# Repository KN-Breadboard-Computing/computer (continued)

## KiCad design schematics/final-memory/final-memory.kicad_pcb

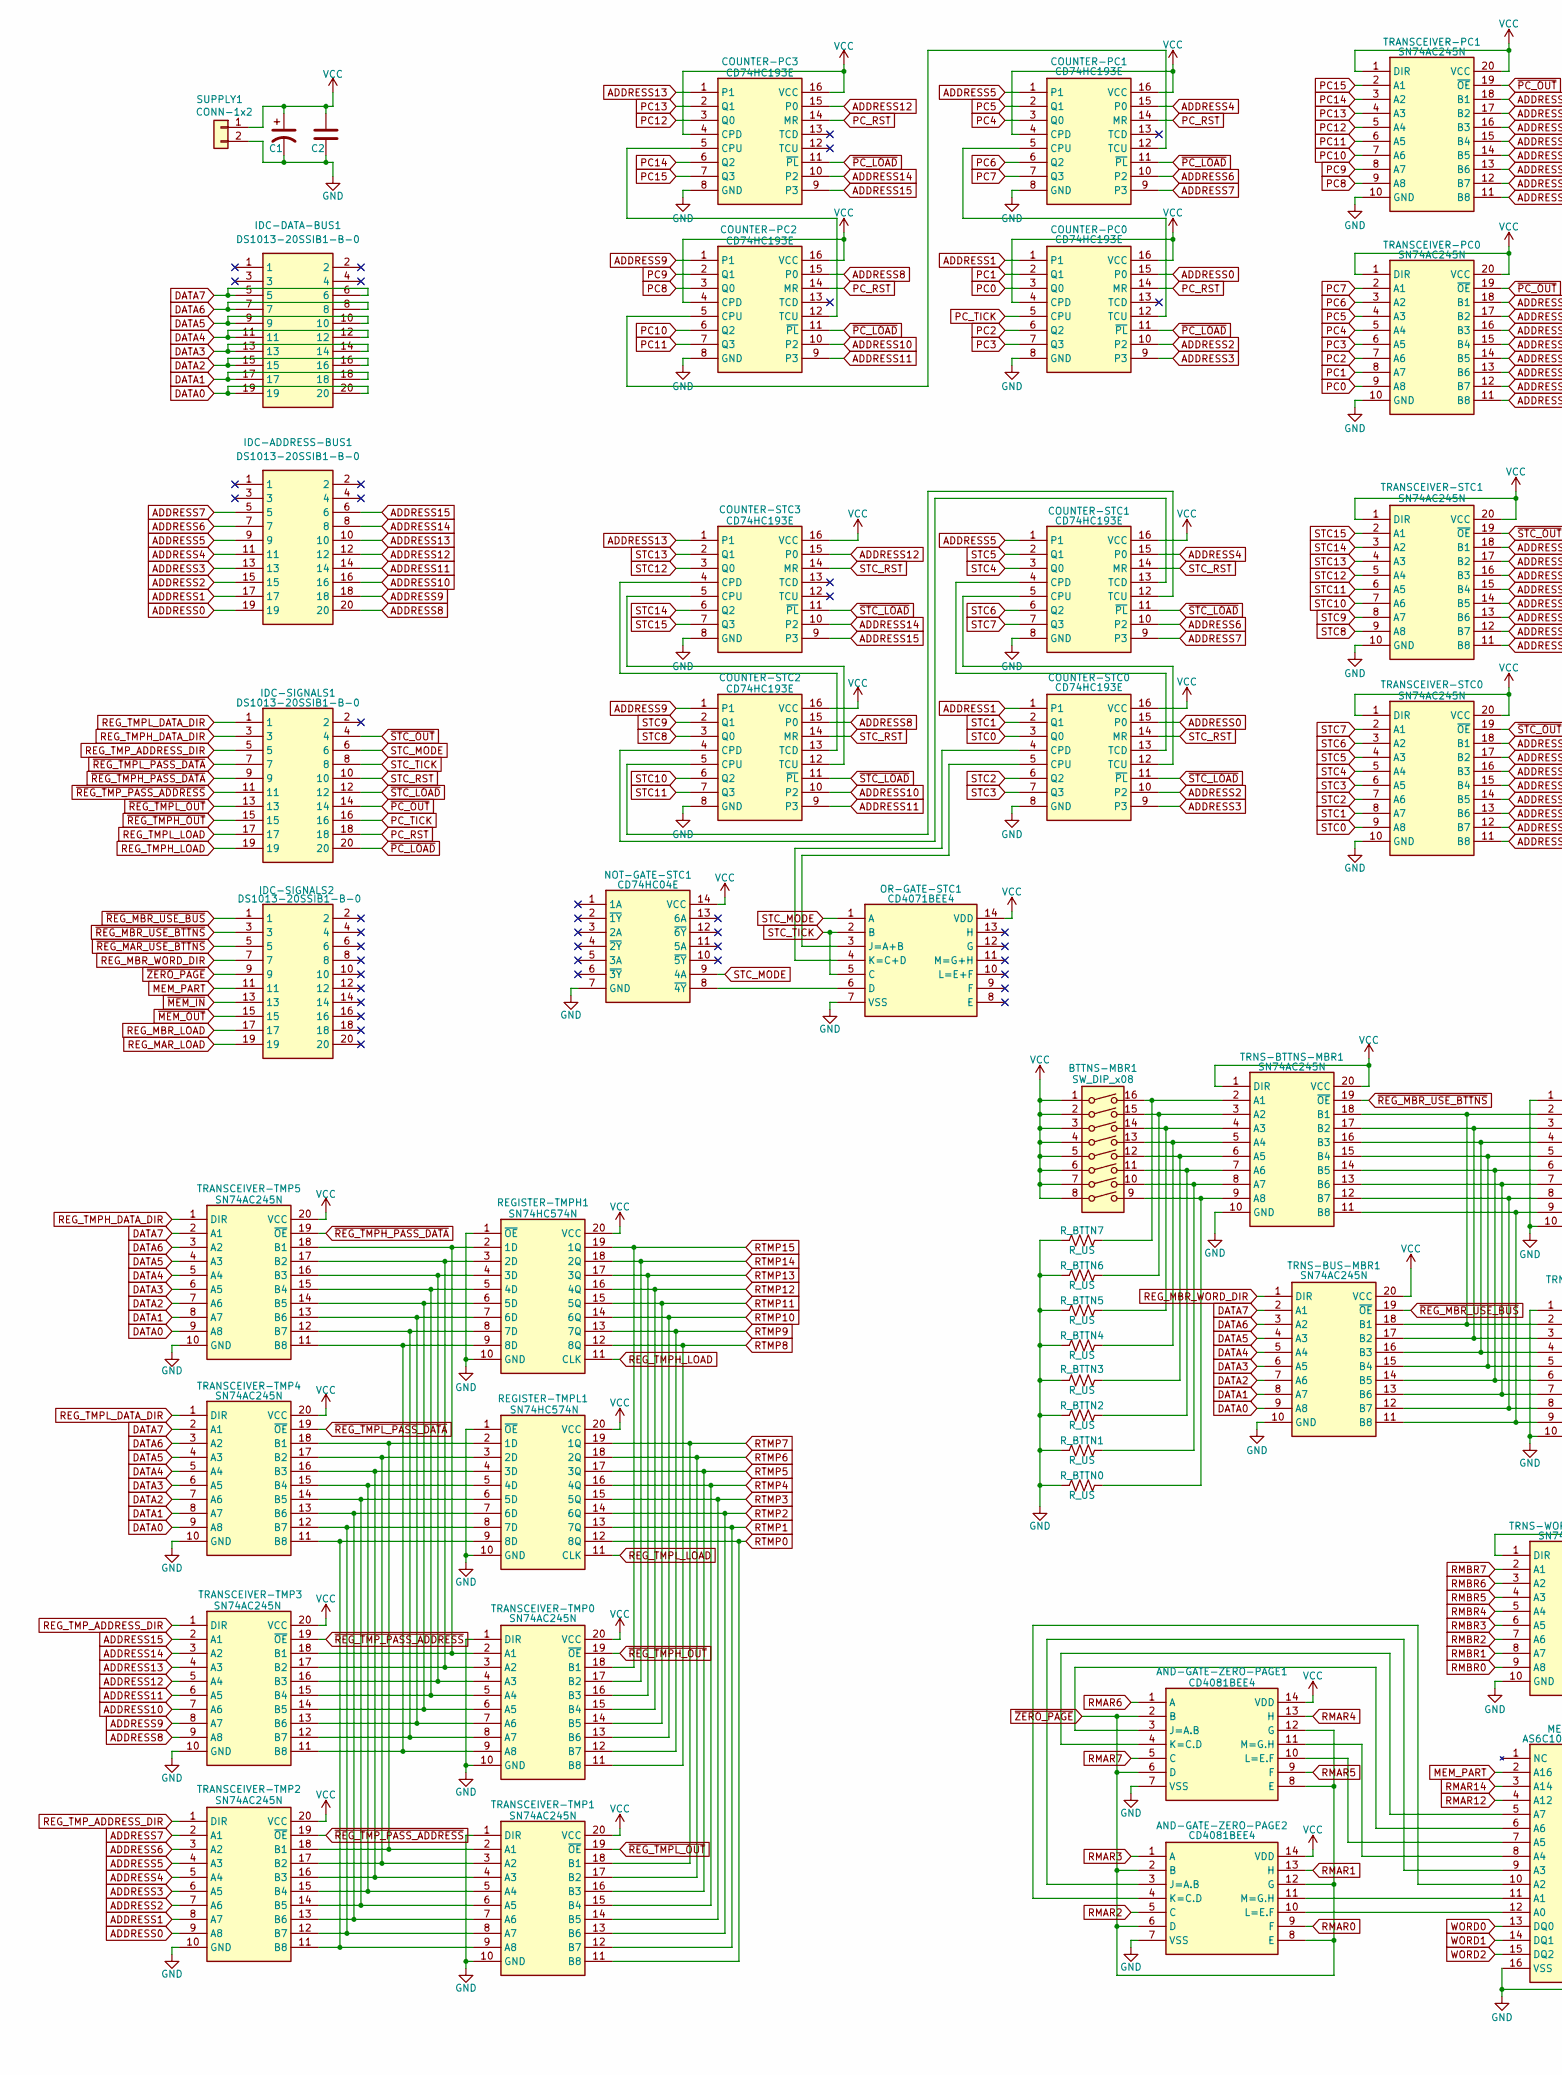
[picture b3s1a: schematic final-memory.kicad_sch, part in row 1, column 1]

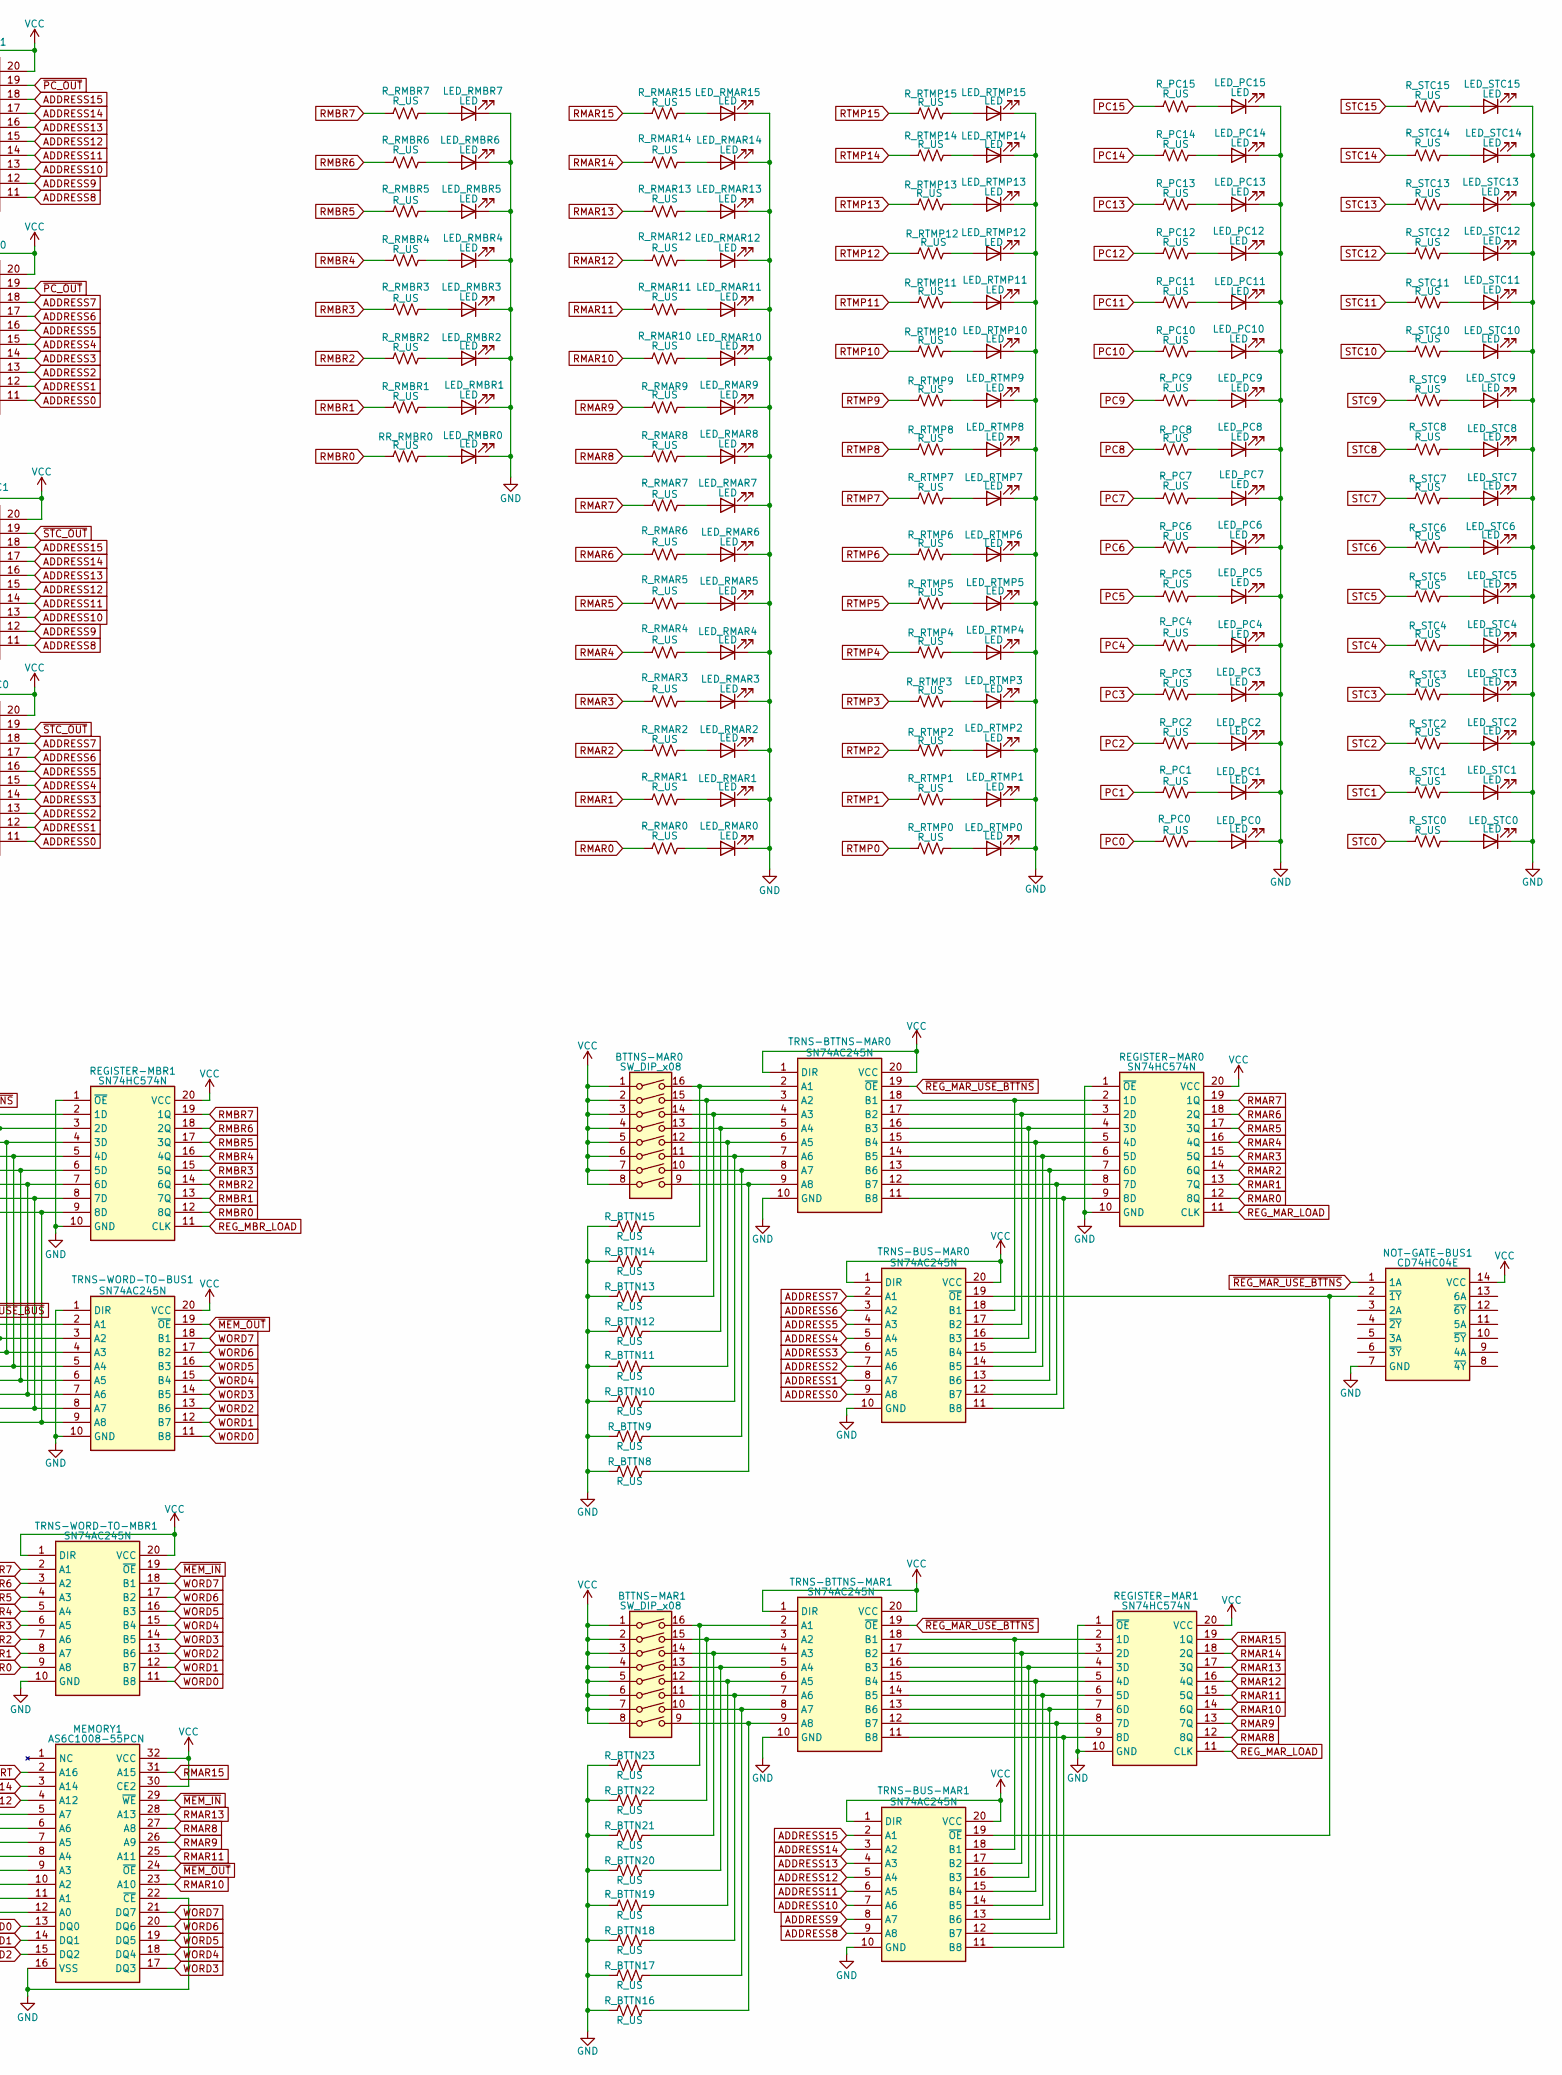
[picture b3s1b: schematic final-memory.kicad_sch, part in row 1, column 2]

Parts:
AND-GATE-ZERO-PAGE1, AND-GATE-ZERO-PAGE2: CD4081BEE4; DIP-14_W7.62mm; Mouser Part Number 595-CD4081BEE4
BTTNS-MAR0, BTTNS-MAR1: SW_DIP_x08; SW_DIP_SPSTx08_Slide_6.7x21.88mm_W7.62mm_P2.54mm_LowProfile
BTTNS-MBR1: SW_DIP_x08; SW_DIP_SPSTx08_Slide_6.7x21.88mm_W7.62mm_P2.54mm_LowProfile
C1: C_Polarized_US; CP_Radial_D5.0mm_P2.50mm
C2: C; C_Disc_D3.0mm_W1.6mm_P2.50mm
COUNTER-PC0, COUNTER-PC1, COUNTER-PC2, COUNTER-PC3: CD74HC193E; DIP-16_W7.62mm; Mouser Part Number 595-CD74HC193E
COUNTER-STC0, COUNTER-STC1, COUNTER-STC2, COUNTER-STC3: CD74HC193E; DIP-16_W7.62mm; Mouser Part Number 595-CD74HC193E
IDC-ADDRESS-BUS1: DS1013-20SSIB1-B-0; PinSocket_2x10_P2.54mm_Vertical; Manufacturer_Part_Number DS1013-20SSIB1-B-0
IDC-DATA-BUS1: DS1013-20SSIB1-B-0; PinSocket_2x10_P2.54mm_Vertical; Manufacturer_Part_Number DS1013-20SSIB1-B-0
IDC-SIGNALS1, IDC-SIGNALS2: DS1013-20SSIB1-B-0; PinSocket_2x10_P2.54mm_Vertical; Manufacturer_Part_Number DS1013-20SSIB1-B-0
LED_PC0, LED_PC1, LED_PC2, LED_PC3, LED_PC4, LED_PC5, LED_PC6, LED_PC7, LED_PC8, LED_PC9, LED_PC10, LED_PC11, LED_PC12, LED_PC13, LED_PC14, LED_PC15: LED; LED_D5.0mm_FlatTop
LED_RMAR0, LED_RMAR1, LED_RMAR2, LED_RMAR3, LED_RMAR4, LED_RMAR5, LED_RMAR6, LED_RMAR7, LED_RMAR8, LED_RMAR9, LED_RMAR10, LED_RMAR11, LED_RMAR12, LED_RMAR13, LED_RMAR14, LED_RMAR15: LED; LED_D5.0mm_FlatTop
LED_RMBR0, LED_RMBR1, LED_RMBR2, LED_RMBR3, LED_RMBR4, LED_RMBR5, LED_RMBR6, LED_RMBR7: LED; LED_D5.0mm_FlatTop
LED_RTMP0, LED_RTMP1, LED_RTMP2, LED_RTMP3, LED_RTMP4, LED_RTMP5, LED_RTMP6, LED_RTMP7, LED_RTMP8, LED_RTMP9, LED_RTMP10, LED_RTMP11, LED_RTMP12, LED_RTMP13, LED_RTMP14, LED_RTMP15: LED; LED_D5.0mm_FlatTop
LED_STC0, LED_STC1, LED_STC2, LED_STC3, LED_STC4, LED_STC5, LED_STC6, LED_STC7, LED_STC8, LED_STC9, LED_STC10, LED_STC11, LED_STC12, LED_STC13, LED_STC14, LED_STC15: LED; LED_D5.0mm_FlatTop
MEMORY1: AS6C1008-55PCN; DIP-32_W15.24mm; Mouser Part Number 913-AS6C1008-55PCN
NOT-GATE-BUS1: CD74HC04E; DIP-14_W7.62mm; Mouser Part Number 595-CD74HC04E
NOT-GATE-STC1: CD74HC04E; DIP-14_W7.62mm; Mouser Part Number 595-CD74HC04E
OR-GATE-STC1: CD4071BEE4; DIP-14_W7.62mm; Mouser Part Number 595-CD4071BEE4
REGISTER-MAR0, REGISTER-MAR1: SN74HC574N; DIP-20_W7.62mm; Mouser Part Number 595-SN74HC574N
REGISTER-MBR1: SN74HC574N; DIP-20_W7.62mm; Mouser Part Number 595-SN74HC574N
REGISTER-TMPH1: SN74HC574N; DIP-20_W7.62mm; Mouser Part Number 595-SN74HC574N
REGISTER-TMPL1: SN74HC574N; DIP-20_W7.62mm; Mouser Part Number 595-SN74HC574N
RR_RMBR0: R_US; R_Axial_DIN0204_L3.6mm_D1.6mm_P7.62mm_Horizontal
R_BTTN0, R_BTTN1, R_BTTN2, R_BTTN3, R_BTTN4, R_BTTN5, R_BTTN6, R_BTTN7, R_BTTN8, R_BTTN9, R_BTTN10, R_BTTN11, R_BTTN12, R_BTTN13, R_BTTN14, R_BTTN15, R_BTTN16, R_BTTN17, R_BTTN18, R_BTTN19, R_BTTN20, R_BTTN21, R_BTTN22, R_BTTN23: R_US; R_Axial_DIN0204_L3.6mm_D1.6mm_P7.62mm_Horizontal
R_PC0, R_PC1, R_PC2, R_PC3, R_PC4, R_PC5, R_PC6, R_PC7, R_PC8, R_PC9, R_PC10, R_PC11, R_PC12, R_PC13, R_PC14, R_PC15: R_US; R_Axial_DIN0204_L3.6mm_D1.6mm_P7.62mm_Horizontal
R_RMAR0, R_RMAR1, R_RMAR2, R_RMAR3, R_RMAR4, R_RMAR5, R_RMAR6, R_RMAR7, R_RMAR8, R_RMAR9, R_RMAR10, R_RMAR11, R_RMAR12, R_RMAR13, R_RMAR14, R_RMAR15: R_US; R_Axial_DIN0204_L3.6mm_D1.6mm_P7.62mm_Horizontal
R_RMBR1, R_RMBR2, R_RMBR3, R_RMBR4, R_RMBR5, R_RMBR6, R_RMBR7: R_US; R_Axial_DIN0204_L3.6mm_D1.6mm_P7.62mm_Horizontal
R_RTMP0, R_RTMP1, R_RTMP2, R_RTMP3, R_RTMP4, R_RTMP5, R_RTMP6, R_RTMP7, R_RTMP8, R_RTMP9, R_RTMP10, R_RTMP11, R_RTMP12, R_RTMP13, R_RTMP14, R_RTMP15: R_US; R_Axial_DIN0204_L3.6mm_D1.6mm_P7.62mm_Horizontal
R_STC0, R_STC1, R_STC2, R_STC3, R_STC4, R_STC5, R_STC6, R_STC7, R_STC8, R_STC9, R_STC10, R_STC11, R_STC12, R_STC13, R_STC14, R_STC15: R_US; R_Axial_DIN0204_L3.6mm_D1.6mm_P7.62mm_Horizontal
SUPPLY1: CONN-1x2; PinHeader_1x02_P2.54mm_Vertical
TRANSCEIVER-PC0, TRANSCEIVER-PC1: SN74AC245N; DIP-20_W7.62mm; Mouser Part Number 595-SN74AC245N
TRANSCEIVER-STC0, TRANSCEIVER-STC1: SN74AC245N; DIP-20_W7.62mm; Mouser Part Number 595-SN74AC245N
TRANSCEIVER-TMP0, TRANSCEIVER-TMP1, TRANSCEIVER-TMP2, TRANSCEIVER-TMP3, TRANSCEIVER-TMP4, TRANSCEIVER-TMP5: SN74AC245N; DIP-20_W7.62mm; Mouser Part Number 595-SN74AC245N
TRNS-BTTNS-MAR0, TRNS-BTTNS-MAR1: SN74AC245N; DIP-20_W7.62mm; Mouser Part Number 595-SN74AC245N
TRNS-BTTNS-MBR1: SN74AC245N; DIP-20_W7.62mm; Mouser Part Number 595-SN74AC245N
TRNS-BUS-MAR0, TRNS-BUS-MAR1: SN74AC245N; DIP-20_W7.62mm; Mouser Part Number 595-SN74AC245N
TRNS-BUS-MBR1: SN74AC245N; DIP-20_W7.62mm; Mouser Part Number 595-SN74AC245N
TRNS-WORD-TO-BUS1: SN74AC245N; DIP-20_W7.62mm; Mouser Part Number 595-SN74AC245N
TRNS-WORD-TO-MBR1: SN74AC245N; DIP-20_W7.62mm; Mouser Part Number 595-SN74AC245N

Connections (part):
ADDRESS0: COUNTER-PC0.15 (P0), COUNTER-STC0.15 (P0), IDC-ADDRESS-BUS1.19, TRANSCEIVER-PC0.11 (B8), TRANSCEIVER-STC0.11 (B8), TRANSCEIVER-TMP2.9 (A8), TRNS-BUS-MAR0.9 (A8)
ADDRESS1: COUNTER-PC0.1, COUNTER-STC0.1, IDC-ADDRESS-BUS1.17, TRANSCEIVER-PC0.12 (B7), TRANSCEIVER-STC0.12 (B7), TRANSCEIVER-TMP2.8 (A7), TRNS-BUS-MAR0.8 (A7)
ADDRESS2: COUNTER-PC0.10 (P2), COUNTER-STC0.10 (P2), IDC-ADDRESS-BUS1.15, TRANSCEIVER-PC0.13 (B6), TRANSCEIVER-STC0.13 (B6), TRANSCEIVER-TMP2.7 (A6), TRNS-BUS-MAR0.7 (A6)
ADDRESS3: COUNTER-PC0.9 (P3), COUNTER-STC0.9 (P3), IDC-ADDRESS-BUS1.13, TRANSCEIVER-PC0.14 (B5), TRANSCEIVER-STC0.14 (B5), TRANSCEIVER-TMP2.6 (A5), TRNS-BUS-MAR0.6 (A5)
ADDRESS4: COUNTER-PC1.15 (P0), COUNTER-STC1.15 (P0), IDC-ADDRESS-BUS1.11, TRANSCEIVER-PC0.15 (B4), TRANSCEIVER-STC0.15 (B4), TRANSCEIVER-TMP2.5 (A4), TRNS-BUS-MAR0.5 (A4)
ADDRESS5: COUNTER-PC1.1, COUNTER-STC1.1, IDC-ADDRESS-BUS1.9, TRANSCEIVER-PC0.16 (B3), TRANSCEIVER-STC0.16 (B3), TRANSCEIVER-TMP2.4 (A3), TRNS-BUS-MAR0.4 (A3)
ADDRESS6: COUNTER-PC1.10 (P2), COUNTER-STC1.10 (P2), IDC-ADDRESS-BUS1.7, TRANSCEIVER-PC0.17 (B2), TRANSCEIVER-STC0.17 (B2), TRANSCEIVER-TMP2.3 (A2), TRNS-BUS-MAR0.3 (A2)
ADDRESS7: COUNTER-PC1.9 (P3), COUNTER-STC1.9 (P3), IDC-ADDRESS-BUS1.5, TRANSCEIVER-PC0.18 (B1), TRANSCEIVER-STC0.18 (B1), TRANSCEIVER-TMP2.2 (A1), TRNS-BUS-MAR0.2 (A1)
ADDRESS8: COUNTER-PC2.15 (P0), COUNTER-STC2.15 (P0), IDC-ADDRESS-BUS1.20, TRANSCEIVER-PC1.11 (B8), TRANSCEIVER-STC1.11 (B8), TRANSCEIVER-TMP3.9 (A8), TRNS-BUS-MAR1.9 (A8)
ADDRESS9: COUNTER-PC2.1, COUNTER-STC2.1, IDC-ADDRESS-BUS1.18, TRANSCEIVER-PC1.12 (B7), TRANSCEIVER-STC1.12 (B7), TRANSCEIVER-TMP3.8 (A7), TRNS-BUS-MAR1.8 (A7)
ADDRESS10: COUNTER-PC2.10 (P2), COUNTER-STC2.10 (P2), IDC-ADDRESS-BUS1.16, TRANSCEIVER-PC1.13 (B6), TRANSCEIVER-STC1.13 (B6), TRANSCEIVER-TMP3.7 (A6), TRNS-BUS-MAR1.7 (A6)
ADDRESS11: COUNTER-PC2.9 (P3), COUNTER-STC2.9 (P3), IDC-ADDRESS-BUS1.14, TRANSCEIVER-PC1.14 (B5), TRANSCEIVER-STC1.14 (B5), TRANSCEIVER-TMP3.6 (A5), TRNS-BUS-MAR1.6 (A5)
ADDRESS12: COUNTER-PC3.15 (P0), COUNTER-STC3.15 (P0), IDC-ADDRESS-BUS1.12, TRANSCEIVER-PC1.15 (B4), TRANSCEIVER-STC1.15 (B4), TRANSCEIVER-TMP3.5 (A4), TRNS-BUS-MAR1.5 (A4)
ADDRESS13: COUNTER-PC3.1, COUNTER-STC3.1, IDC-ADDRESS-BUS1.10, TRANSCEIVER-PC1.16 (B3), TRANSCEIVER-STC1.16 (B3), TRANSCEIVER-TMP3.4 (A3), TRNS-BUS-MAR1.4 (A3)
ADDRESS14: COUNTER-PC3.10 (P2), COUNTER-STC3.10 (P2), IDC-ADDRESS-BUS1.8, TRANSCEIVER-PC1.17 (B2), TRANSCEIVER-STC1.17 (B2), TRANSCEIVER-TMP3.3 (A2), TRNS-BUS-MAR1.3 (A2)
ADDRESS15: COUNTER-PC3.9 (P3), COUNTER-STC3.9 (P3), IDC-ADDRESS-BUS1.6, TRANSCEIVER-PC1.18 (B1), TRANSCEIVER-STC1.18 (B1), TRANSCEIVER-TMP3.2 (A1), TRNS-BUS-MAR1.2 (A1)
DATA0: IDC-DATA-BUS1.19, IDC-DATA-BUS1.20, TRANSCEIVER-TMP4.9 (A8), TRANSCEIVER-TMP5.9 (A8), TRNS-BUS-MBR1.9 (A8)
DATA1: IDC-DATA-BUS1.17, IDC-DATA-BUS1.18, TRANSCEIVER-TMP4.8 (A7), TRANSCEIVER-TMP5.8 (A7), TRNS-BUS-MBR1.8 (A7)
DATA2: IDC-DATA-BUS1.15, IDC-DATA-BUS1.16, TRANSCEIVER-TMP4.7 (A6), TRANSCEIVER-TMP5.7 (A6), TRNS-BUS-MBR1.7 (A6)
DATA3: IDC-DATA-BUS1.13, IDC-DATA-BUS1.14, TRANSCEIVER-TMP4.6 (A5), TRANSCEIVER-TMP5.6 (A5), TRNS-BUS-MBR1.6 (A5)
DATA4: IDC-DATA-BUS1.11, IDC-DATA-BUS1.12, TRANSCEIVER-TMP4.5 (A4), TRANSCEIVER-TMP5.5 (A4), TRNS-BUS-MBR1.5 (A4)
DATA5: IDC-DATA-BUS1.9, IDC-DATA-BUS1.10, TRANSCEIVER-TMP4.4 (A3), TRANSCEIVER-TMP5.4 (A3), TRNS-BUS-MBR1.4 (A3)
DATA6: IDC-DATA-BUS1.7, IDC-DATA-BUS1.8, TRANSCEIVER-TMP4.3 (A2), TRANSCEIVER-TMP5.3 (A2), TRNS-BUS-MBR1.3 (A2)
DATA7: IDC-DATA-BUS1.5, IDC-DATA-BUS1.6, TRANSCEIVER-TMP4.2 (A1), TRANSCEIVER-TMP5.2 (A1), TRNS-BUS-MBR1.2 (A1)
GND: AND-GATE-ZERO-PAGE1.7 (VSS), AND-GATE-ZERO-PAGE2.7 (VSS), C1.2, C2.2, COUNTER-PC0.8 (GND), COUNTER-PC1.8 (GND), COUNTER-PC2.8 (GND), COUNTER-PC3.8 (GND), COUNTER-STC0.8 (GND), COUNTER-STC1.8 (GND), COUNTER-STC2.8 (GND), COUNTER-STC3.8 (GND), LED_PC0.1 (K), LED_PC1.1 (K), LED_PC2.1 (K), LED_PC3.1 (K), LED_PC4.1 (K), LED_PC5.1 (K), LED_PC6.1 (K), LED_PC7.1 (K), LED_PC8.1 (K), LED_PC9.1 (K), LED_PC10.1 (K), LED_PC11.1 (K), LED_PC12.1 (K), LED_PC13.1 (K), LED_PC14.1 (K), LED_PC15.1 (K), LED_RMAR0.1 (K), LED_RMAR1.1 (K), LED_RMAR2.1 (K), LED_RMAR3.1 (K), LED_RMAR4.1 (K), LED_RMAR5.1 (K), LED_RMAR6.1 (K), LED_RMAR7.1 (K), LED_RMAR8.1 (K), LED_RMAR9.1 (K), LED_RMAR10.1 (K), LED_RMAR11.1 (K), LED_RMAR12.1 (K), LED_RMAR13.1 (K), LED_RMAR14.1 (K), LED_RMAR15.1 (K), LED_RMBR0.1 (K), LED_RMBR1.1 (K), LED_RMBR2.1 (K), LED_RMBR3.1 (K), LED_RMBR4.1 (K), LED_RMBR5.1 (K), LED_RMBR6.1 (K), LED_RMBR7.1 (K), LED_RTMP0.1 (K), LED_RTMP1.1 (K), LED_RTMP2.1 (K), LED_RTMP3.1 (K), LED_RTMP4.1 (K), LED_RTMP5.1 (K), LED_RTMP6.1 (K), LED_RTMP7.1 (K), LED_RTMP8.1 (K), LED_RTMP9.1 (K), LED_RTMP10.1 (K), LED_RTMP11.1 (K), LED_RTMP12.1 (K), LED_RTMP13.1 (K), LED_RTMP14.1 (K), LED_RTMP15.1 (K), LED_STC0.1 (K), LED_STC1.1 (K), LED_STC2.1 (K), LED_STC3.1 (K), LED_STC4.1 (K), LED_STC5.1 (K), LED_STC6.1 (K), LED_STC7.1 (K), LED_STC8.1 (K), LED_STC9.1 (K), LED_STC10.1 (K), LED_STC11.1 (K), LED_STC12.1 (K), LED_STC13.1 (K)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
MEM_PART: IDC-SIGNALS2.11, MEMORY1.2 (A16)
unnamed: AND-GATE-ZERO-PAGE1.3 (J=A.B), MEMORY1.6 (A6)
unnamed: AND-GATE-ZERO-PAGE1.4 (K=C.D), MEMORY1.5 (A7)
unnamed: AND-GATE-ZERO-PAGE1.10 (L=E.F), MEMORY1.7 (A5)
unnamed: AND-GATE-ZERO-PAGE1.11 (M=G.H), MEMORY1.8 (A4)
unnamed: AND-GATE-ZERO-PAGE2.3 (J=A.B), MEMORY1.9 (A3)
unnamed: AND-GATE-ZERO-PAGE2.4 (K=C.D), MEMORY1.10 (A2)
unnamed: AND-GATE-ZERO-PAGE2.10 (L=E.F), MEMORY1.12 (A0)
unnamed: AND-GATE-ZERO-PAGE2.11 (M=G.H), MEMORY1.11 (A1)
unnamed: COUNTER-PC0.12 (TCU), COUNTER-PC1.5 (CPU)
unnamed: COUNTER-PC1.12 (TCU), COUNTER-PC2.5 (CPU)
unnamed: COUNTER-PC2.12 (TCU), COUNTER-PC3.5 (CPU)
unnamed: COUNTER-STC0.4 (CPD), OR-GATE-STC1.4 (K=C+D)
unnamed: COUNTER-STC0.5 (CPU), OR-GATE-STC1.3 (J=A+B)
unnamed: COUNTER-STC0.13 (TCD), COUNTER-STC1.4 (CPD)
unnamed: COUNTER-STC0.12 (TCU), COUNTER-STC1.5 (CPU)
unnamed: COUNTER-STC1.13 (TCD), COUNTER-STC2.4 (CPD)
unnamed: COUNTER-STC1.12 (TCU), COUNTER-STC2.5 (CPU)
unnamed: COUNTER-STC2.13 (TCD), COUNTER-STC3.4 (CPD)
unnamed: COUNTER-STC2.12 (TCU), COUNTER-STC3.5 (CPU)
unnamed: LED_PC0.2 (A), R_PC0.2
unnamed: LED_PC1.2 (A), R_PC1.2
unnamed: LED_PC2.2 (A), R_PC2.2
unnamed: LED_PC3.2 (A), R_PC3.2
unnamed: LED_PC4.2 (A), R_PC4.2
unnamed: LED_PC5.2 (A), R_PC5.2
unnamed: LED_PC6.2 (A), R_PC6.2
unnamed: LED_PC7.2 (A), R_PC7.2
unnamed: LED_PC8.2 (A), R_PC8.2
unnamed: LED_PC9.2 (A), R_PC9.2
unnamed: LED_PC10.2 (A), R_PC10.2
unnamed: LED_PC11.2 (A), R_PC11.2
unnamed: LED_PC12.2 (A), R_PC12.2
unnamed: LED_PC13.2 (A), R_PC13.2
unnamed: LED_PC14.2 (A), R_PC14.2
unnamed: LED_PC15.2 (A), R_PC15.2
unnamed: LED_RMAR0.2 (A), R_RMAR0.2
unnamed: LED_RMAR1.2 (A), R_RMAR1.2
unnamed: LED_RMAR2.2 (A), R_RMAR2.2
unnamed: LED_RMAR3.2 (A), R_RMAR3.2
unnamed: LED_RMAR4.2 (A), R_RMAR4.2
unnamed: LED_RMAR5.2 (A), R_RMAR5.2
unnamed: LED_RMAR6.2 (A), R_RMAR6.2
unnamed: LED_RMAR7.2 (A), R_RMAR7.2
unnamed: LED_RMAR8.2 (A), R_RMAR8.2
unnamed: LED_RMAR9.2 (A), R_RMAR9.2
unnamed: LED_RMAR10.2 (A), R_RMAR10.2
unnamed: LED_RMAR11.2 (A), R_RMAR11.2
unnamed: LED_RMAR12.2 (A), R_RMAR12.2
unnamed: LED_RMAR13.2 (A), R_RMAR13.2
unnamed: LED_RMAR14.2 (A), R_RMAR14.2
unnamed: LED_RMAR15.2 (A), R_RMAR15.2
unnamed: LED_RMBR0.2 (A), RR_RMBR0.2
unnamed: LED_RMBR1.2 (A), R_RMBR1.2
unnamed: LED_RMBR2.2 (A), R_RMBR2.2
unnamed: LED_RMBR3.2 (A), R_RMBR3.2
unnamed: LED_RMBR4.2 (A), R_RMBR4.2
unnamed: LED_RMBR5.2 (A), R_RMBR5.2
unnamed: LED_RMBR6.2 (A), R_RMBR6.2
unnamed: LED_RMBR7.2 (A), R_RMBR7.2
unnamed: LED_RTMP0.2 (A), R_RTMP0.2
unnamed: LED_RTMP1.2 (A), R_RTMP1.2
unnamed: LED_RTMP2.2 (A), R_RTMP2.2
unnamed: LED_RTMP3.2 (A), R_RTMP3.2
unnamed: LED_RTMP4.2 (A), R_RTMP4.2
unnamed: LED_RTMP5.2 (A), R_RTMP5.2
unnamed: LED_RTMP6.2 (A), R_RTMP6.2
unnamed: LED_RTMP7.2 (A), R_RTMP7.2
unnamed: LED_RTMP8.2 (A), R_RTMP8.2
unnamed: LED_RTMP9.2 (A), R_RTMP9.2
unnamed: LED_RTMP10.2 (A), R_RTMP10.2
unnamed: LED_RTMP11.2 (A), R_RTMP11.2
unnamed: LED_RTMP12.2 (A), R_RTMP12.2
unnamed: LED_RTMP13.2 (A), R_RTMP13.2
unnamed: LED_RTMP14.2 (A), R_RTMP14.2
unnamed: LED_RTMP15.2 (A), R_RTMP15.2
unnamed: LED_STC0.2 (A), R_STC0.2
unnamed: LED_STC1.2 (A), R_STC1.2
unnamed: LED_STC2.2 (A), R_STC2.2
unnamed: LED_STC3.2 (A), R_STC3.2
unnamed: LED_STC4.2 (A), R_STC4.2
unnamed: LED_STC5.2 (A), R_STC5.2
unnamed: LED_STC6.2 (A), R_STC6.2
unnamed: LED_STC7.2 (A), R_STC7.2
unnamed: LED_STC8.2 (A), R_STC8.2
unnamed: LED_STC9.2 (A), R_STC9.2
unnamed: LED_STC10.2 (A), R_STC10.2
unnamed: LED_STC11.2 (A), R_STC11.2
unnamed: LED_STC12.2 (A), R_STC12.2
unnamed: LED_STC13.2 (A), R_STC13.2
unnamed: LED_STC14.2 (A), R_STC14.2
unnamed: LED_STC15.2 (A), R_STC15.2
unnamed: NOT-GATE-BUS1.2 (~1Y), TRNS-BUS-MAR0.19 (~OE), TRNS-BUS-MAR1.19 (~OE)
unnamed: NOT-GATE-STC1.8 (~4Y), OR-GATE-STC1.6 (D)
unnamed: REGISTER-MAR0.2 (1D), TRNS-BTTNS-MAR0.18 (B1), TRNS-BUS-MAR0.18 (B1)
unnamed: REGISTER-MAR0.3 (2D), TRNS-BTTNS-MAR0.17 (B2), TRNS-BUS-MAR0.17 (B2)
unnamed: REGISTER-MAR0.4 (3D), TRNS-BTTNS-MAR0.16 (B3), TRNS-BUS-MAR0.16 (B3)
unnamed: REGISTER-MAR0.5 (4D), TRNS-BTTNS-MAR0.15 (B4), TRNS-BUS-MAR0.15 (B4)
unnamed: REGISTER-MAR0.6 (5D), TRNS-BTTNS-MAR0.14 (B5), TRNS-BUS-MAR0.14 (B5)
unnamed: REGISTER-MAR0.7 (6D), TRNS-BTTNS-MAR0.13 (B6), TRNS-BUS-MAR0.13 (B6)
unnamed: REGISTER-MAR0.8 (7D), TRNS-BTTNS-MAR0.12 (B7), TRNS-BUS-MAR0.12 (B7)
unnamed: REGISTER-MAR0.9 (8D), TRNS-BTTNS-MAR0.11 (B8), TRNS-BUS-MAR0.11 (B8)
unnamed: REGISTER-MAR1.2 (1D), TRNS-BTTNS-MAR1.18 (B1), TRNS-BUS-MAR1.18 (B1)
unnamed: REGISTER-MAR1.3 (2D), TRNS-BTTNS-MAR1.17 (B2), TRNS-BUS-MAR1.17 (B2)
unnamed: REGISTER-MAR1.4 (3D), TRNS-BTTNS-MAR1.16 (B3), TRNS-BUS-MAR1.16 (B3)
unnamed: REGISTER-MAR1.5 (4D), TRNS-BTTNS-MAR1.15 (B4), TRNS-BUS-MAR1.15 (B4)
unnamed: REGISTER-MAR1.6 (5D), TRNS-BTTNS-MAR1.14 (B5), TRNS-BUS-MAR1.14 (B5)
unnamed: REGISTER-MAR1.7 (6D), TRNS-BTTNS-MAR1.13 (B6), TRNS-BUS-MAR1.13 (B6)
unnamed: REGISTER-MAR1.8 (7D), TRNS-BTTNS-MAR1.12 (B7), TRNS-BUS-MAR1.12 (B7)
unnamed: REGISTER-MAR1.9 (8D), TRNS-BTTNS-MAR1.11 (B8), TRNS-BUS-MAR1.11 (B8)
unnamed: REGISTER-MBR1.2 (1D), TRNS-BTTNS-MBR1.18 (B1), TRNS-BUS-MBR1.18 (B1), TRNS-WORD-TO-BUS1.2 (A1)
unnamed: REGISTER-MBR1.3 (2D), TRNS-BTTNS-MBR1.17 (B2), TRNS-BUS-MBR1.17 (B2), TRNS-WORD-TO-BUS1.3 (A2)
unnamed: REGISTER-MBR1.4 (3D), TRNS-BTTNS-MBR1.16 (B3), TRNS-BUS-MBR1.16 (B3), TRNS-WORD-TO-BUS1.4 (A3)
unnamed: REGISTER-MBR1.5 (4D), TRNS-BTTNS-MBR1.15 (B4), TRNS-BUS-MBR1.15 (B4), TRNS-WORD-TO-BUS1.5 (A4)
unnamed: REGISTER-MBR1.6 (5D), TRNS-BTTNS-MBR1.14 (B5), TRNS-BUS-MBR1.14 (B5), TRNS-WORD-TO-BUS1.6 (A5)
unnamed: REGISTER-MBR1.7 (6D), TRNS-BTTNS-MBR1.13 (B6), TRNS-BUS-MBR1.13 (B6), TRNS-WORD-TO-BUS1.7 (A6)
unnamed: REGISTER-MBR1.8 (7D), TRNS-BTTNS-MBR1.12 (B7), TRNS-BUS-MBR1.12 (B7), TRNS-WORD-TO-BUS1.8 (A7)
unnamed: REGISTER-MBR1.9 (8D), TRNS-BTTNS-MBR1.11 (B8), TRNS-BUS-MBR1.11 (B8), TRNS-WORD-TO-BUS1.9 (A8)
unnamed: REGISTER-TMPH1.2 (1D), TRANSCEIVER-TMP0.2 (A1), TRANSCEIVER-TMP3.18 (B1), TRANSCEIVER-TMP5.18 (B1)
unnamed: REGISTER-TMPH1.3 (2D), TRANSCEIVER-TMP0.3 (A2), TRANSCEIVER-TMP3.17 (B2), TRANSCEIVER-TMP5.17 (B2)
unnamed: REGISTER-TMPH1.4 (3D), TRANSCEIVER-TMP0.4 (A3), TRANSCEIVER-TMP3.16 (B3), TRANSCEIVER-TMP5.16 (B3)
unnamed: REGISTER-TMPH1.5 (4D), TRANSCEIVER-TMP0.5 (A4), TRANSCEIVER-TMP3.15 (B4), TRANSCEIVER-TMP5.15 (B4)
unnamed: REGISTER-TMPH1.6 (5D), TRANSCEIVER-TMP0.6 (A5), TRANSCEIVER-TMP3.14 (B5), TRANSCEIVER-TMP5.14 (B5)
unnamed: REGISTER-TMPH1.7 (6D), TRANSCEIVER-TMP0.7 (A6), TRANSCEIVER-TMP3.13 (B6), TRANSCEIVER-TMP5.13 (B6)
unnamed: REGISTER-TMPH1.8 (7D), TRANSCEIVER-TMP0.8 (A7), TRANSCEIVER-TMP3.12 (B7), TRANSCEIVER-TMP5.12 (B7)
unnamed: REGISTER-TMPH1.9 (8D), TRANSCEIVER-TMP0.9 (A8), TRANSCEIVER-TMP3.11 (B8), TRANSCEIVER-TMP5.11 (B8)
unnamed: REGISTER-TMPL1.2 (1D), TRANSCEIVER-TMP1.2 (A1), TRANSCEIVER-TMP2.18 (B1), TRANSCEIVER-TMP4.18 (B1)
unnamed: REGISTER-TMPL1.3 (2D), TRANSCEIVER-TMP1.3 (A2), TRANSCEIVER-TMP2.17 (B2), TRANSCEIVER-TMP4.17 (B2)
unnamed: REGISTER-TMPL1.4 (3D), TRANSCEIVER-TMP1.4 (A3), TRANSCEIVER-TMP2.16 (B3), TRANSCEIVER-TMP4.16 (B3)
unnamed: REGISTER-TMPL1.5 (4D), TRANSCEIVER-TMP1.5 (A4), TRANSCEIVER-TMP2.15 (B4), TRANSCEIVER-TMP4.15 (B4)
unnamed: REGISTER-TMPL1.6 (5D), TRANSCEIVER-TMP1.6 (A5), TRANSCEIVER-TMP2.14 (B5), TRANSCEIVER-TMP4.14 (B5)
unnamed: REGISTER-TMPL1.7 (6D), TRANSCEIVER-TMP1.7 (A6), TRANSCEIVER-TMP2.13 (B6), TRANSCEIVER-TMP4.13 (B6)
unnamed: REGISTER-TMPL1.8 (7D), TRANSCEIVER-TMP1.8 (A7), TRANSCEIVER-TMP2.12 (B7), TRANSCEIVER-TMP4.12 (B7)
unnamed: REGISTER-TMPL1.9 (8D), TRANSCEIVER-TMP1.9 (A8), TRANSCEIVER-TMP2.11 (B8), TRANSCEIVER-TMP4.11 (B8)
unnamed: BTTNS-MAR0.16, R_BTTN15.2, TRNS-BTTNS-MAR0.2 (A1)
unnamed: BTTNS-MAR0.15, R_BTTN14.2, TRNS-BTTNS-MAR0.3 (A2)
unnamed: BTTNS-MAR0.14, R_BTTN13.2, TRNS-BTTNS-MAR0.4 (A3)
unnamed: BTTNS-MAR0.13, R_BTTN12.2, TRNS-BTTNS-MAR0.5 (A4)
unnamed: BTTNS-MAR0.12, R_BTTN11.2, TRNS-BTTNS-MAR0.6 (A5)
unnamed: BTTNS-MAR0.11, R_BTTN10.2, TRNS-BTTNS-MAR0.7 (A6)
unnamed: BTTNS-MAR0.10, R_BTTN9.2, TRNS-BTTNS-MAR0.8 (A7)
unnamed: BTTNS-MAR0.9, R_BTTN8.2, TRNS-BTTNS-MAR0.9 (A8)
unnamed: BTTNS-MAR1.16, R_BTTN23.2, TRNS-BTTNS-MAR1.2 (A1)
unnamed: BTTNS-MAR1.15, R_BTTN22.2, TRNS-BTTNS-MAR1.3 (A2)
unnamed: BTTNS-MAR1.14, R_BTTN21.2, TRNS-BTTNS-MAR1.4 (A3)
unnamed: BTTNS-MAR1.13, R_BTTN20.2, TRNS-BTTNS-MAR1.5 (A4)
unnamed: BTTNS-MAR1.12, R_BTTN19.2, TRNS-BTTNS-MAR1.6 (A5)
unnamed: BTTNS-MAR1.11, R_BTTN18.2, TRNS-BTTNS-MAR1.7 (A6)
unnamed: BTTNS-MAR1.10, R_BTTN17.2, TRNS-BTTNS-MAR1.8 (A7)
unnamed: BTTNS-MAR1.9, R_BTTN16.2, TRNS-BTTNS-MAR1.9 (A8)
unnamed: BTTNS-MBR1.16, R_BTTN7.2, TRNS-BTTNS-MBR1.2 (A1)
unnamed: BTTNS-MBR1.15, R_BTTN6.2, TRNS-BTTNS-MBR1.3 (A2)
unnamed: BTTNS-MBR1.14, R_BTTN5.2, TRNS-BTTNS-MBR1.4 (A3)
unnamed: BTTNS-MBR1.13, R_BTTN4.2, TRNS-BTTNS-MBR1.5 (A4)
unnamed: BTTNS-MBR1.12, R_BTTN3.2, TRNS-BTTNS-MBR1.6 (A5)
unnamed: BTTNS-MBR1.11, R_BTTN2.2, TRNS-BTTNS-MBR1.7 (A6)
unnamed: BTTNS-MBR1.10, R_BTTN1.2, TRNS-BTTNS-MBR1.8 (A7)
unnamed: BTTNS-MBR1.9, R_BTTN0.2, TRNS-BTTNS-MBR1.9 (A8)
PC0: COUNTER-PC0.3 (Q0), R_PC0.1, TRANSCEIVER-PC0.9 (A8)
PC1: COUNTER-PC0.2 (Q1), R_PC1.1, TRANSCEIVER-PC0.8 (A7)
PC2: COUNTER-PC0.6 (Q2), R_PC2.1, TRANSCEIVER-PC0.7 (A6)
PC3: COUNTER-PC0.7 (Q3), R_PC3.1, TRANSCEIVER-PC0.6 (A5)
PC4: COUNTER-PC1.3 (Q0), R_PC4.1, TRANSCEIVER-PC0.5 (A4)
PC5: COUNTER-PC1.2 (Q1), R_PC5.1, TRANSCEIVER-PC0.4 (A3)
PC6: COUNTER-PC1.6 (Q2), R_PC6.1, TRANSCEIVER-PC0.3 (A2)
PC7: COUNTER-PC1.7 (Q3), R_PC7.1, TRANSCEIVER-PC0.2 (A1)
PC8: COUNTER-PC2.3 (Q0), R_PC8.1, TRANSCEIVER-PC1.9 (A8)
PC9: COUNTER-PC2.2 (Q1), R_PC9.1, TRANSCEIVER-PC1.8 (A7)
PC10: COUNTER-PC2.6 (Q2), R_PC10.1, TRANSCEIVER-PC1.7 (A6)
PC11: COUNTER-PC2.7 (Q3), R_PC11.1, TRANSCEIVER-PC1.6 (A5)
PC12: COUNTER-PC3.3 (Q0), R_PC12.1, TRANSCEIVER-PC1.5 (A4)
PC13: COUNTER-PC3.2 (Q1), R_PC13.1, TRANSCEIVER-PC1.4 (A3)
PC14: COUNTER-PC3.6 (Q2), R_PC14.1, TRANSCEIVER-PC1.3 (A2)
PC15: COUNTER-PC3.7 (Q3), R_PC15.1, TRANSCEIVER-PC1.2 (A1)
PC_RST: COUNTER-PC0.14 (MR), COUNTER-PC1.14 (MR), COUNTER-PC2.14 (MR), COUNTER-PC3.14 (MR), IDC-SIGNALS1.18
PC_TICK: COUNTER-PC0.5 (CPU), IDC-SIGNALS1.16
REG_MAR_LOAD: IDC-SIGNALS2.19, REGISTER-MAR0.11 (CLK), REGISTER-MAR1.11 (CLK)
REG_MBR_LOAD: IDC-SIGNALS2.17, REGISTER-MBR1.11 (CLK)
REG_MBR_WORD_DIR: IDC-SIGNALS2.7, TRNS-BUS-MBR1.1 (DIR)
REG_TMPH_DATA_DIR: IDC-SIGNALS1.3, TRANSCEIVER-TMP5.1 (DIR)
REG_TMPH_LOAD: IDC-SIGNALS1.19, REGISTER-TMPH1.11 (CLK)
REG_TMPL_DATA_DIR: IDC-SIGNALS1.1, TRANSCEIVER-TMP4.1 (DIR)
REG_TMPL_LOAD: IDC-SIGNALS1.17, REGISTER-TMPL1.11 (CLK)
REG_TMP_ADDRESS_DIR: IDC-SIGNALS1.5, TRANSCEIVER-TMP2.1 (DIR), TRANSCEIVER-TMP3.1 (DIR)
RMAR0: AND-GATE-ZERO-PAGE2.9 (F), REGISTER-MAR0.12 (8Q), R_RMAR0.1
RMAR1: AND-GATE-ZERO-PAGE2.13 (H), REGISTER-MAR0.13 (7Q), R_RMAR1.1
RMAR2: AND-GATE-ZERO-PAGE2.5 (C), REGISTER-MAR0.14 (6Q), R_RMAR2.1
RMAR3: AND-GATE-ZERO-PAGE2.1 (A), REGISTER-MAR0.15 (5Q), R_RMAR3.1
RMAR4: AND-GATE-ZERO-PAGE1.13 (H), REGISTER-MAR0.16 (4Q), R_RMAR4.1
RMAR5: AND-GATE-ZERO-PAGE1.9 (F), REGISTER-MAR0.17 (3Q), R_RMAR5.1
RMAR6: AND-GATE-ZERO-PAGE1.1 (A), REGISTER-MAR0.18 (2Q), R_RMAR6.1
RMAR7: AND-GATE-ZERO-PAGE1.5 (C), REGISTER-MAR0.19 (1Q), R_RMAR7.1
RMAR8: MEMORY1.27 (A8), REGISTER-MAR1.12 (8Q), R_RMAR8.1
RMAR9: MEMORY1.26 (A9), REGISTER-MAR1.13 (7Q), R_RMAR9.1
RMAR10: MEMORY1.23 (A10), REGISTER-MAR1.14 (6Q), R_RMAR10.1
RMAR11: MEMORY1.25 (A11), REGISTER-MAR1.15 (5Q), R_RMAR11.1
RMAR12: MEMORY1.4 (A12), REGISTER-MAR1.16 (4Q), R_RMAR12.1
RMAR13: MEMORY1.28 (A13), REGISTER-MAR1.17 (3Q), R_RMAR13.1
RMAR14: MEMORY1.3 (A14), REGISTER-MAR1.18 (2Q), R_RMAR14.1
RMAR15: MEMORY1.31 (A15), REGISTER-MAR1.19 (1Q), R_RMAR15.1
RMBR0: REGISTER-MBR1.12 (8Q), RR_RMBR0.1, TRNS-WORD-TO-MBR1.9 (A8)
RMBR1: REGISTER-MBR1.13 (7Q), R_RMBR1.1, TRNS-WORD-TO-MBR1.8 (A7)
RMBR2: REGISTER-MBR1.14 (6Q), R_RMBR2.1, TRNS-WORD-TO-MBR1.7 (A6)
RMBR3: REGISTER-MBR1.15 (5Q), R_RMBR3.1, TRNS-WORD-TO-MBR1.6 (A5)
RMBR4: REGISTER-MBR1.16 (4Q), R_RMBR4.1, TRNS-WORD-TO-MBR1.5 (A4)
RMBR5: REGISTER-MBR1.17 (3Q), R_RMBR5.1, TRNS-WORD-TO-MBR1.4 (A3)
RMBR6: REGISTER-MBR1.18 (2Q), R_RMBR6.1, TRNS-WORD-TO-MBR1.3 (A2)
RMBR7: REGISTER-MBR1.19 (1Q), R_RMBR7.1, TRNS-WORD-TO-MBR1.2 (A1)
RTMP0: REGISTER-TMPL1.12 (8Q), R_RTMP0.1, TRANSCEIVER-TMP1.11 (B8)
RTMP1: REGISTER-TMPL1.13 (7Q), R_RTMP1.1, TRANSCEIVER-TMP1.12 (B7)
RTMP2: REGISTER-TMPL1.14 (6Q), R_RTMP2.1, TRANSCEIVER-TMP1.13 (B6)
RTMP3: REGISTER-TMPL1.15 (5Q), R_RTMP3.1, TRANSCEIVER-TMP1.14 (B5)
RTMP4: REGISTER-TMPL1.16 (4Q), R_RTMP4.1, TRANSCEIVER-TMP1.15 (B4)
RTMP5: REGISTER-TMPL1.17 (3Q), R_RTMP5.1, TRANSCEIVER-TMP1.16 (B3)
RTMP6: REGISTER-TMPL1.18 (2Q), R_RTMP6.1, TRANSCEIVER-TMP1.17 (B2)
RTMP7: REGISTER-TMPL1.19 (1Q), R_RTMP7.1, TRANSCEIVER-TMP1.18 (B1)
RTMP8: REGISTER-TMPH1.12 (8Q), R_RTMP8.1, TRANSCEIVER-TMP0.11 (B8)
RTMP9: REGISTER-TMPH1.13 (7Q), R_RTMP9.1, TRANSCEIVER-TMP0.12 (B7)
RTMP10: REGISTER-TMPH1.14 (6Q), R_RTMP10.1, TRANSCEIVER-TMP0.13 (B6)
RTMP11: REGISTER-TMPH1.15 (5Q), R_RTMP11.1, TRANSCEIVER-TMP0.14 (B5)
RTMP12: REGISTER-TMPH1.16 (4Q), R_RTMP12.1, TRANSCEIVER-TMP0.15 (B4)
RTMP13: REGISTER-TMPH1.17 (3Q), R_RTMP13.1, TRANSCEIVER-TMP0.16 (B3)
RTMP14: REGISTER-TMPH1.18 (2Q), R_RTMP14.1, TRANSCEIVER-TMP0.17 (B2)
RTMP15: REGISTER-TMPH1.19 (1Q), R_RTMP15.1, TRANSCEIVER-TMP0.18 (B1)
STC0: COUNTER-STC0.3 (Q0), R_STC0.1, TRANSCEIVER-STC0.9 (A8)
STC1: COUNTER-STC0.2 (Q1), R_STC1.1, TRANSCEIVER-STC0.8 (A7)
STC2: COUNTER-STC0.6 (Q2), R_STC2.1, TRANSCEIVER-STC0.7 (A6)
STC3: COUNTER-STC0.7 (Q3), R_STC3.1, TRANSCEIVER-STC0.6 (A5)
STC4: COUNTER-STC1.3 (Q0), R_STC4.1, TRANSCEIVER-STC0.5 (A4)
STC5: COUNTER-STC1.2 (Q1), R_STC5.1, TRANSCEIVER-STC0.4 (A3)
STC6: COUNTER-STC1.6 (Q2), R_STC6.1, TRANSCEIVER-STC0.3 (A2)
STC7: COUNTER-STC1.7 (Q3), R_STC7.1, TRANSCEIVER-STC0.2 (A1)
STC8: COUNTER-STC2.3 (Q0), R_STC8.1, TRANSCEIVER-STC1.9 (A8)
STC9: COUNTER-STC2.2 (Q1), R_STC9.1, TRANSCEIVER-STC1.8 (A7)
STC10: COUNTER-STC2.6 (Q2), R_STC10.1, TRANSCEIVER-STC1.7 (A6)
STC11: COUNTER-STC2.7 (Q3), R_STC11.1, TRANSCEIVER-STC1.6 (A5)
STC12: COUNTER-STC3.3 (Q0), R_STC12.1, TRANSCEIVER-STC1.5 (A4)
STC13: COUNTER-STC3.2 (Q1), R_STC13.1, TRANSCEIVER-STC1.4 (A3)
STC14: COUNTER-STC3.6 (Q2), R_STC14.1, TRANSCEIVER-STC1.3 (A2)
STC15: COUNTER-STC3.7 (Q3), R_STC15.1, TRANSCEIVER-STC1.2 (A1)
STC_MODE: IDC-SIGNALS1.6, NOT-GATE-STC1.9 (4A), OR-GATE-STC1.1 (A)
STC_RST: COUNTER-STC0.14 (MR), COUNTER-STC1.14 (MR), COUNTER-STC2.14 (MR), COUNTER-STC3.14 (MR), IDC-SIGNALS1.10
STC_TICK: IDC-SIGNALS1.8, OR-GATE-STC1.2 (B), OR-GATE-STC1.5 (C)
VCC: AND-GATE-ZERO-PAGE1.14 (VDD), AND-GATE-ZERO-PAGE2.14 (VDD), BTTNS-MAR0.1, BTTNS-MAR0.2, BTTNS-MAR0.3, BTTNS-MAR0.4, BTTNS-MAR0.5, BTTNS-MAR0.6, BTTNS-MAR0.7, BTTNS-MAR0.8, BTTNS-MAR1.1, BTTNS-MAR1.2, BTTNS-MAR1.3, BTTNS-MAR1.4, BTTNS-MAR1.5, BTTNS-MAR1.6, BTTNS-MAR1.7, BTTNS-MAR1.8, BTTNS-MBR1.1, BTTNS-MBR1.2, BTTNS-MBR1.3, BTTNS-MBR1.4, BTTNS-MBR1.5, BTTNS-MBR1.6, BTTNS-MBR1.7, BTTNS-MBR1.8, C1.1, C2.1, COUNTER-PC0.4 (CPD), COUNTER-PC0.16 (VCC), COUNTER-PC1.4 (CPD), COUNTER-PC1.16 (VCC), COUNTER-PC2.4 (CPD), COUNTER-PC2.16 (VCC), COUNTER-PC3.4 (CPD), COUNTER-PC3.16 (VCC), COUNTER-STC0.16 (VCC), COUNTER-STC1.16 (VCC), COUNTER-STC2.16 (VCC), COUNTER-STC3.16 (VCC), MEMORY1.30 (CE2), MEMORY1.32 (VCC), NOT-GATE-BUS1.14 (VCC), NOT-GATE-STC1.14 (VCC), OR-GATE-STC1.14 (VDD), REGISTER-MAR0.20 (VCC), REGISTER-MAR1.20 (VCC), REGISTER-MBR1.20 (VCC), REGISTER-TMPH1.20 (VCC), REGISTER-TMPL1.20 (VCC), SUPPLY1.1, TRANSCEIVER-PC0.1 (DIR), TRANSCEIVER-PC0.20 (VCC), TRANSCEIVER-PC1.1 (DIR), TRANSCEIVER-PC1.20 (VCC), TRANSCEIVER-STC0.1 (DIR), TRANSCEIVER-STC0.20 (VCC), TRANSCEIVER-STC1.1 (DIR), TRANSCEIVER-STC1.20 (VCC), TRANSCEIVER-TMP0.20 (VCC), TRANSCEIVER-TMP1.20 (VCC), TRANSCEIVER-TMP2.20 (VCC), TRANSCEIVER-TMP3.20 (VCC), TRANSCEIVER-TMP4.20 (VCC), TRANSCEIVER-TMP5.20 (VCC), TRNS-BTTNS-MAR0.1 (DIR), TRNS-BTTNS-MAR0.20 (VCC), TRNS-BTTNS-MAR1.1 (DIR), TRNS-BTTNS-MAR1.20 (VCC), TRNS-BTTNS-MBR1.1 (DIR), TRNS-BTTNS-MBR1.20 (VCC), TRNS-BUS-MAR0.1 (DIR), TRNS-BUS-MAR0.20 (VCC), TRNS-BUS-MAR1.1 (DIR), TRNS-BUS-MAR1.20 (VCC), TRNS-BUS-MBR1.20 (VCC), TRNS-WORD-TO-BUS1.20 (VCC), TRNS-WORD-TO-MBR1.1 (DIR), TRNS-WORD-TO-MBR1.20 (VCC)
WORD0: MEMORY1.13 (DQ0), TRNS-WORD-TO-BUS1.11 (B8), TRNS-WORD-TO-MBR1.11 (B8)
WORD1: MEMORY1.14 (DQ1), TRNS-WORD-TO-BUS1.12 (B7), TRNS-WORD-TO-MBR1.12 (B7)
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
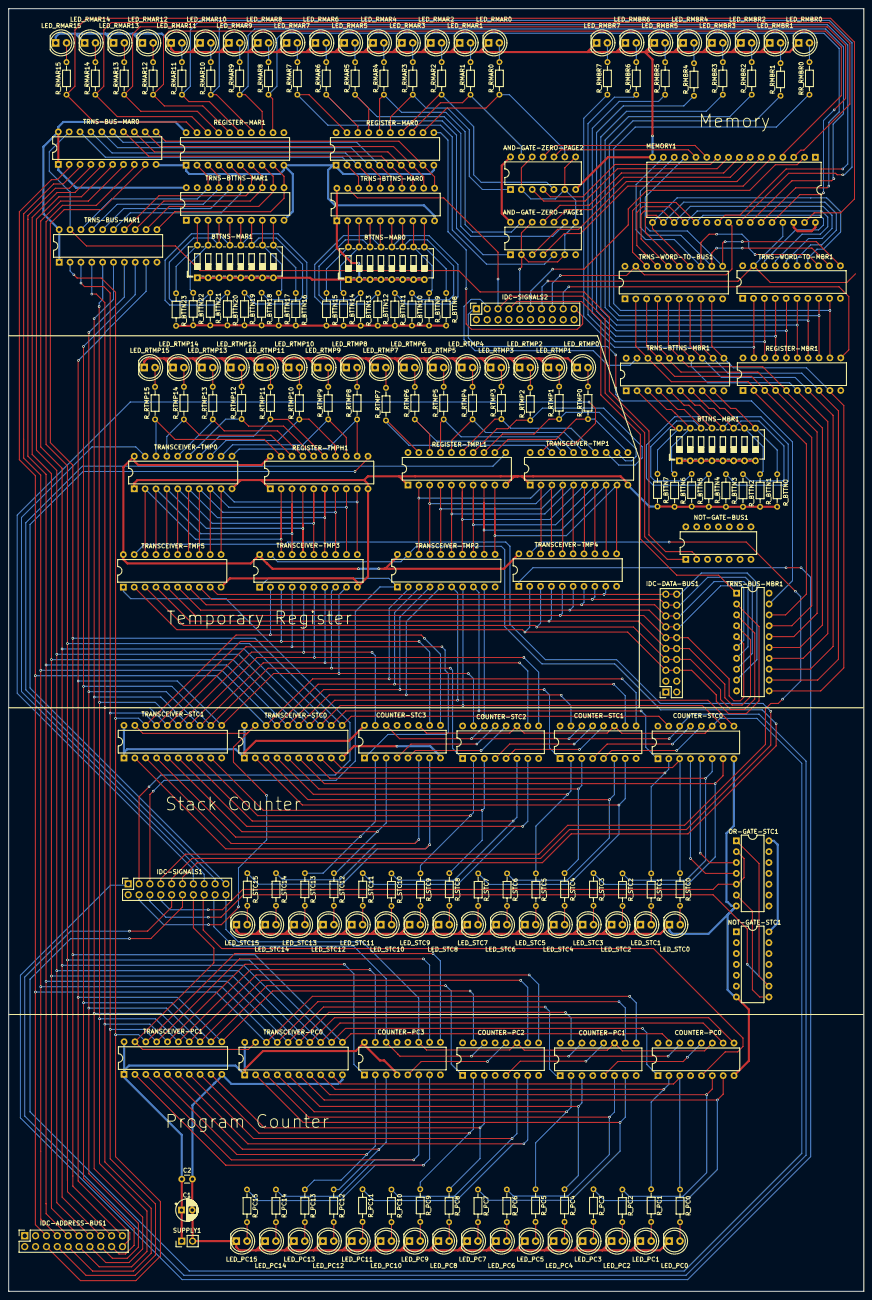
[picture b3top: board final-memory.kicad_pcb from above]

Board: 2 copper layers, 200.0 x 300.0 mm, 215 parts (0 on the bottom side), 292 nets.
